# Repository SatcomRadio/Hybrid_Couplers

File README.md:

# Hybrid coupler boards for making circular polarization

This repo consists of different boards that use different devices to get [circular polarized](https://satcomradio.github.io/#/antennas/polarization) antennas. 

#### Please make sure to visit the [satcom radio website](https://satcomradio.github.io/) for more information

All the PCB boards have a version that where you can use SMA connectors or soldered wires.  
If you want to use the SMA connector boards, you will need to buy:

```
3x SMA connectors for PCB with 1.6mm spacing (aliexpress.com/item/10000000835065.html)

```

Important!

You must connect them correctly! Each port has to be a "dipole".  
Depending on their orientation you will get RHCP or LHCP.

------

## Ordering the PCB:

Download the Gerber file you want from this repo and order it a jlcpcb with the default options.  
The only option I've changed is to remove the manufacture code mark

------

## CMX03A03:

- [SMA version](./GERBER-CmxSma.zip)  
- [Soldered wires version](./GERBER-CmxRf.zip)

Most compact option for high power. Can handle 200W

### BOM:

```
1x CMX03A03 (aliexpress.com/item/1005008506296292.html)
1x G150N 50 ohm RF load (aliexpress.com/item/32909755238.html)

```
----

## RF Power:

- [SMA version](./GERBER-RfPowerSma.zip)  
- [Soldered wires version](./GERBER-RfPowerRf.zip)

Can handle 200W.  
Probably an old model made by "Florida RF Labs"
There's no information about this coupler but it's usually sold with a 50 ohm resistance for free.

### BOM:

```
1x RF Power coupler (aliexpress.com/item/32886665884.html)

This resistance is often given for free when you buy the coupler:
1x RF 32-7001 50 ohm RF load (aliexpress.com/i/1005006266356008.html)

```
----

## Anaren 10260-3:

- [SMA version](./GERBER-AnarenSma.zip)  
- [Soldered wires version](./GERBER-AnarenRf.zip)

Can handle 250W.  
Outdated so it's difficult to find. Usually it's sold on ebay.

### BOM:

```
1x Anaren 10260-3
1x G150N 50 ohm RF load (aliexpress.com/item/32909755238.html)

```
----

## QCN3:

- [SMA version](./GERBER-CmxSma.zip)  
- [Soldered wires version](./GERBER-Qcn3Rf.zip)

Most compact option. Can handle 15W.  
To be used only with handheld radios.

### BOM:

```
1x QCN-3 (aliexpress.com/item/1005002788551103.html)
2x SMD resistor 2512 100Ω 2W resistor (https://es.aliexpress.com/item/1005007255020731.html)

```
----

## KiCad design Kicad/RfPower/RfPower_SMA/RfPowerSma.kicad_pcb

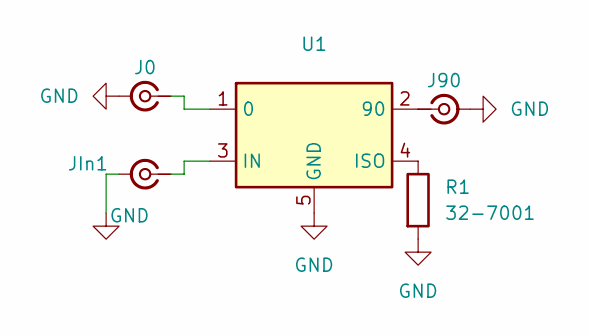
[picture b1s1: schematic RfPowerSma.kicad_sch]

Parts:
J0, J90: SMA_Samtec_SMA-J-P-X-ST-EM1_EdgeMount
JIn1: SMA_Samtec_SMA-J-P-X-ST-EM1_EdgeMount
R1: 32-7001
U1: RfPower

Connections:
GND: J0.2 (Ext), J90.2 (Ext), JIn1.2 (Ext), R1.2, U1.5 (GND)
unnamed: J0.1 (In), U1.1 (0)
unnamed: J90.1 (In), U1.2 (90)
unnamed: JIn1.1 (In), U1.3 (IN)
unnamed: R1.1, U1.4 (ISO)

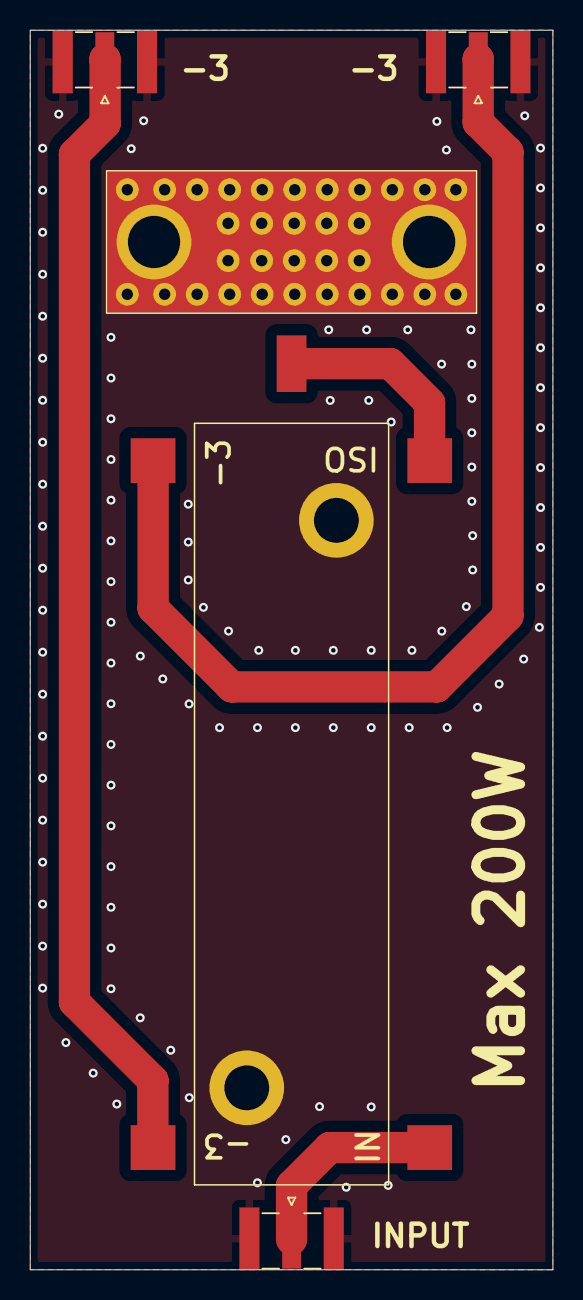
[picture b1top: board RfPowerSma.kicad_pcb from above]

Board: 2 copper layers, 35.0 x 83.0 mm, 5 parts (0 on the bottom side), 5 nets.

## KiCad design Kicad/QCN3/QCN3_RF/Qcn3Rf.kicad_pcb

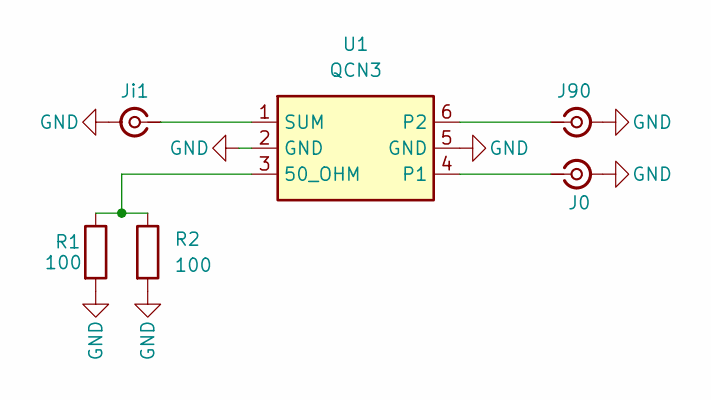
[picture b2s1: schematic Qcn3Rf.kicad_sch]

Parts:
J0, J90: Conn_Coaxial_Small; Wire connector_S
Ji1: Conn_Coaxial_Small; Wire connector_S
R1, R2: 100; R_2512_6332Metric_Pad1.40x3.35mm_HandSolder
U1: QCN3

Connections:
GND: J0.2 (Ext), J90.2 (Ext), Ji1.2 (Ext), R1.2, R2.2, U1.2 (GND), U1.5 (GND)
unnamed: J0.1 (In), U1.4 (P1)
unnamed: J90.1 (In), U1.6 (P2)
unnamed: Ji1.1 (In), U1.1 (SUM)
unnamed: R1.1, R2.1, U1.3 (50_OHM)

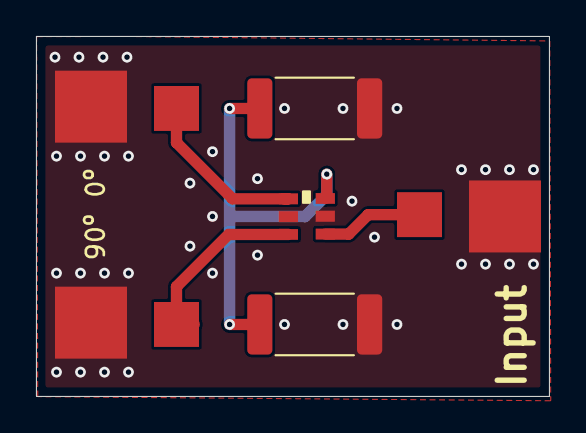
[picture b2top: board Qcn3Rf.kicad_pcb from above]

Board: 2 copper layers, 28.5 x 20.0 mm, 6 parts (0 on the bottom side), 5 nets.

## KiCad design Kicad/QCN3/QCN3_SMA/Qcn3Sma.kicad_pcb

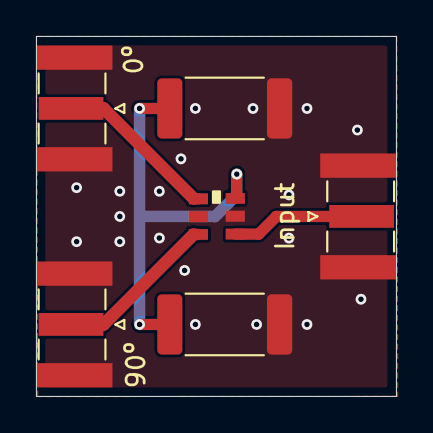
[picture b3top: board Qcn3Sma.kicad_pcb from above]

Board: 2 copper layers, 20.0 x 20.0 mm, 6 parts (0 on the bottom side), 5 nets.

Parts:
0º, 90º: Conn_Coaxial_Small; SMA_Samtec_SMA-J-P-X-ST-EM1_EdgeMount
Input: Conn_Coaxial_Small; SMA_Samtec_SMA-J-P-X-ST-EM1_EdgeMount
R1, R2: 100; R_2512_6332Metric_Pad1.40x3.35mm_HandSolder
U1: QCN3

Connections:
GND: 0º.2 (Ext), 90º.2 (Ext), Input.2 (Ext), R1.2, R2.2, U1.2 (GND), U1.5 (GND)
unnamed: 0º.1 (In), U1.4 (P1)
unnamed: 90º.1 (In), U1.6 (P2)
unnamed: Input.1 (In), U1.1 (SUM)
unnamed: R1.1, R2.1, U1.3 (50_OHM)

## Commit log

2025-05-15 Better images
2025-05-15 Update images
2025-05-15 Fix sizes
2025-05-15 Spacing
2025-05-15 Fix texts
2025-05-16 Added data
